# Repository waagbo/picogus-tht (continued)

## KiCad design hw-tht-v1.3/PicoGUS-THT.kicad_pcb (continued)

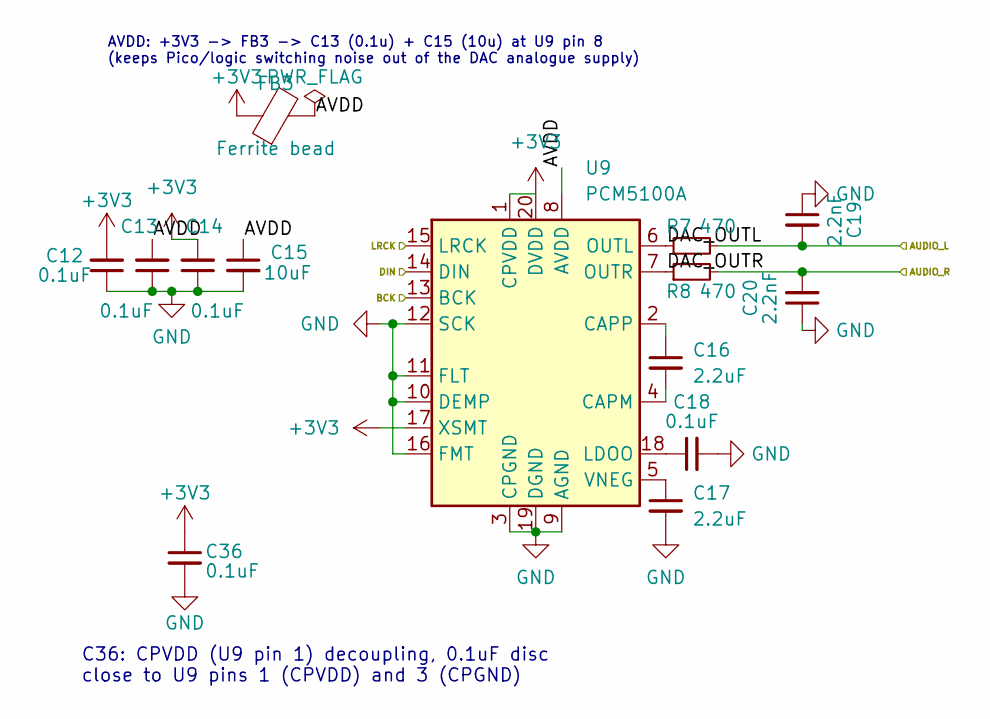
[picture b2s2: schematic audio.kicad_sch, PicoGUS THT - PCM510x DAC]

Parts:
C12, C13, C14, C18, C36: 0.1uF; C_Disc_D5.0mm_W2.5mm_P5.00mm; MPN RDER71H104K0M1H03A; DigiKey 490-9144-1-ND
C15: 10uF; C_Disc_D5.0mm_W2.5mm_P5.00mm; MPN RCER71H106MWK1H03B; DigiKey 490-11888-ND
C16, C17: 2.2uF; C_Disc_D5.0mm_W2.5mm_P5.00mm; MPN FG24X7R1H225KRT06; DigiKey 445-173378-1-ND
C19, C20: 2.2nF; C_Disc_D5.0mm_W2.5mm_P5.00mm; MPN FG28C0G1H222JNT06; DigiKey 445-173487-1-ND
FB3: Ferrite bead; R_Axial_DIN0309_L9.0mm_D3.2mm_P12.70mm_Horizontal; MPN 2743002112; DigiKey 1934-1477-1-ND
R7, R8: 470; R_Axial_DIN0207_L6.3mm_D2.5mm_P10.16mm_Horizontal; MPN RNMF14FTC470R; DigiKey S470CACT-ND
U9: PCM5100A; TSSOP-20_4.4x6.5mm_P0.65mm_HandSolder_TestPads; MPN PCM5100APWR; DigiKey 296-36705-1-ND

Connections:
+3V3: C12.2, C14.2, C36.1, FB3.1, U9.1 (CPVDD), U9.17 (XSMT), U9.20 (DVDD); also elsewhere on the board
/PCM5100 audio/AUDIO_L: C19.2, R7.2; also elsewhere on the board
/PCM5100 audio/AUDIO_R: C20.2, R8.2; also elsewhere on the board
/PCM5100 audio/AVDD: C13.2, C15.1, FB3.2, U9.8 (AVDD)
/PCM5100 audio/DAC_OUTL: R7.1, U9.6 (OUTL)
/PCM5100 audio/DAC_OUTR: R8.1, U9.7 (OUTR)
BCK: U9.13 (BCK); also elsewhere on the board
DIN: U9.14 (DIN); also elsewhere on the board
GND: C12.1, C13.1, C14.1, C15.2, C17.2, C18.2, C19.1, C20.1, C36.2, U9.3 (CPGND), U9.9 (AGND), U9.10 (DEMP), U9.11 (FLT), U9.12 (SCK), U9.16 (FMT), U9.19 (DGND); also elsewhere on the board
LRCK: U9.15 (LRCK); also elsewhere on the board
unnamed: C16.2, U9.4 (CAPM)
unnamed: C16.1, U9.2 (CAPP)
unnamed: C18.1, U9.18 (LDOO)
unnamed: C17.1, U9.5 (VNEG)

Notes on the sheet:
AVDD: +3V3 -> FB3 -> C13 (0.1u) + C15 (10u) at U9 pin 8 (keeps Pico/logic switching noise out of the DAC analogue supply)
C36: CPVDD (U9 pin 1) decoupling, 0.1uF disc close to U9 pins 1 (CPVDD) and 3 (CPGND)

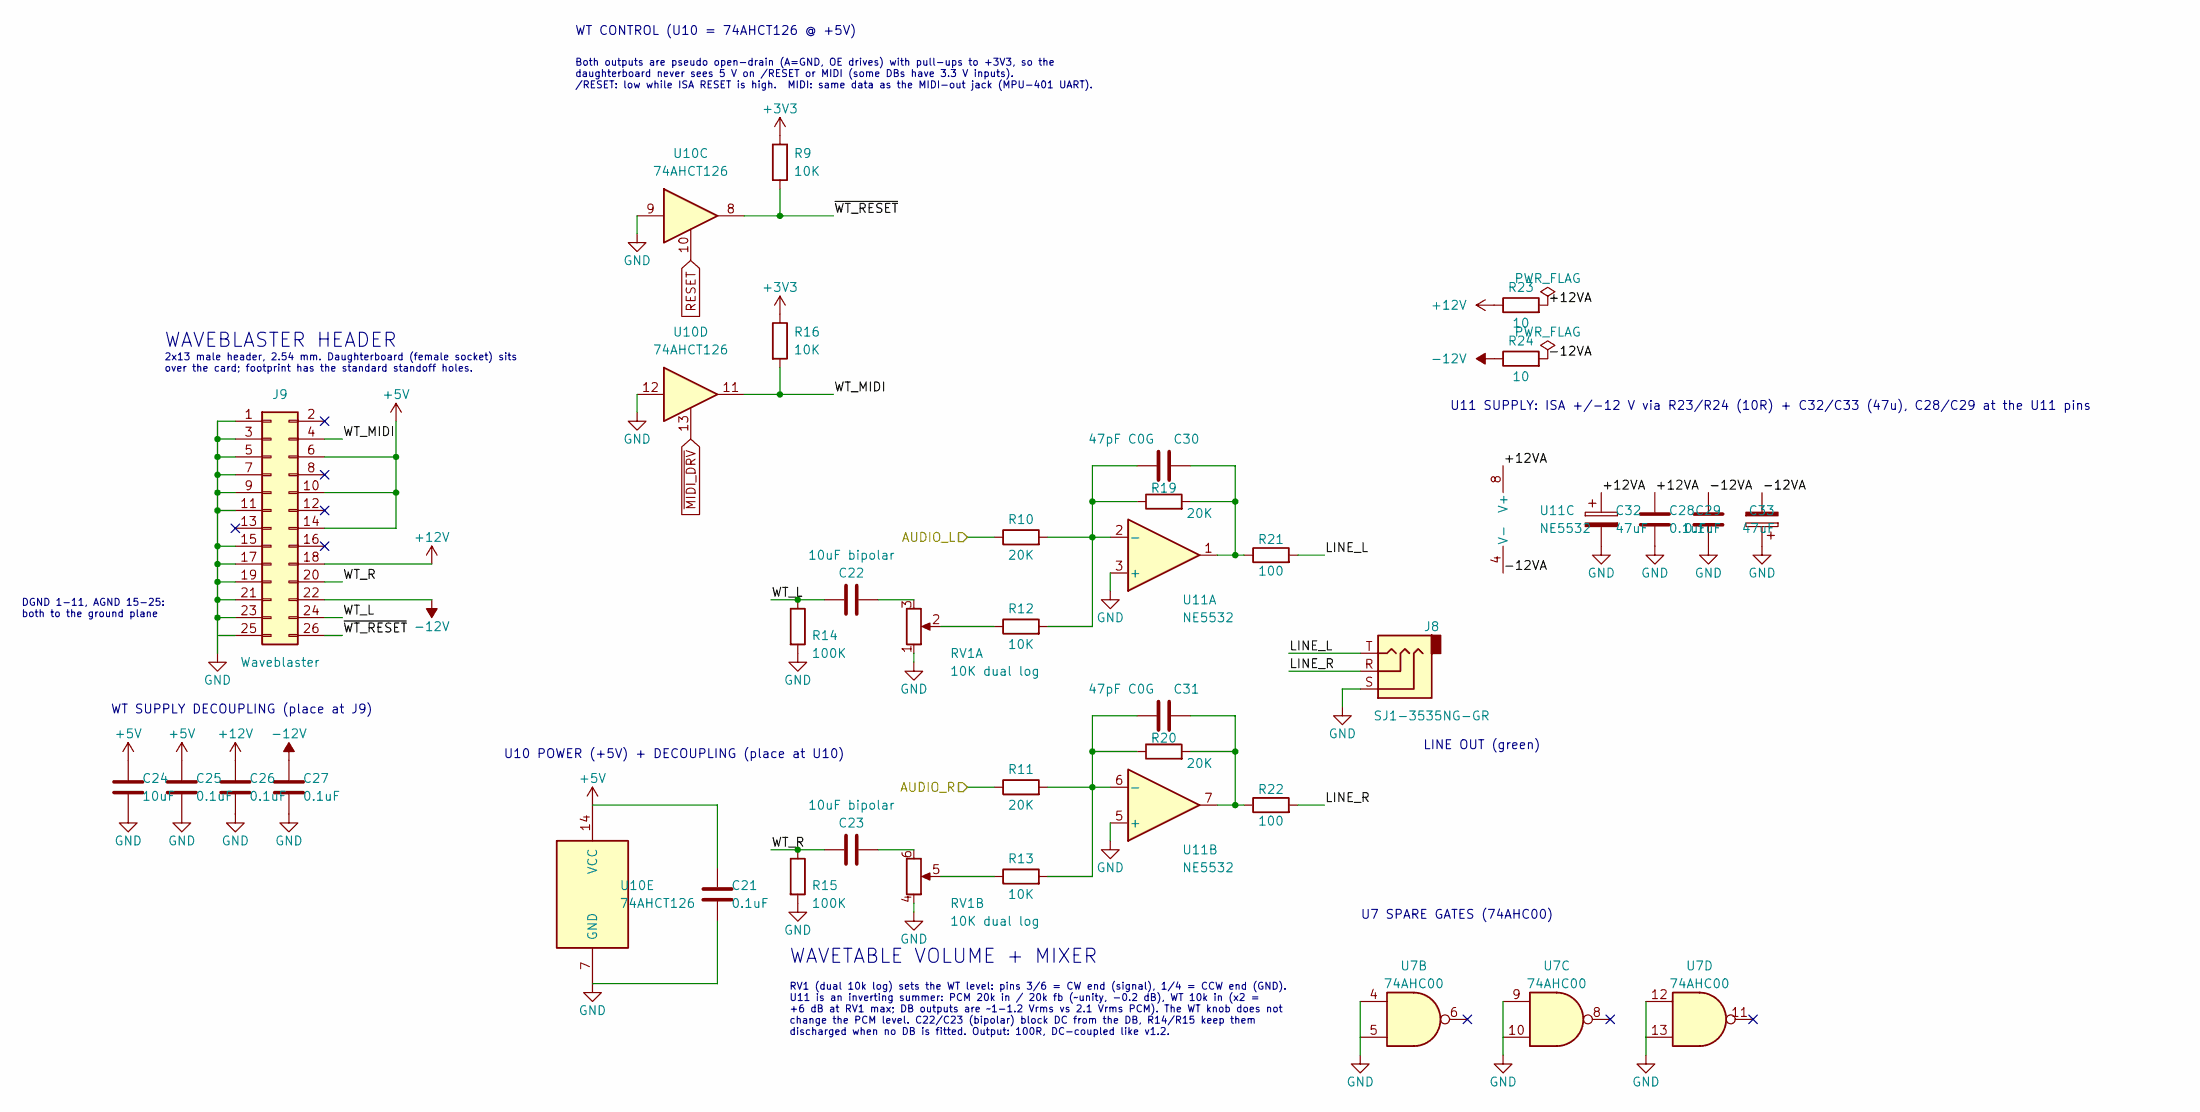
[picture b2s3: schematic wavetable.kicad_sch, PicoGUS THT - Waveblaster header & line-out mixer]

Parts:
C21, C25, C26, C27, C28, C29: 0.1uF; C_Disc_D5.0mm_W2.5mm_P5.00mm; MPN RDER71H104K0M1H03A; DigiKey 490-9144-1-ND
C22, C23: 10uF bipolar; C_Radial_D6.3mm_H11.0mm_P2.50mm; MPN ECE-A1HN100U; DigiKey P1280-ND
C24: 10uF; C_Disc_D5.0mm_W2.5mm_P5.00mm; MPN RCER71H106MWK1H03B; DigiKey 490-11888-ND
C30, C31: 47pF C0G; C_Disc_D5.0mm_W2.5mm_P5.00mm; MPN K470J15C0GF5TH5; DigiKey BC1038CT-ND
C32, C33: 47uF; CP_Radial_D5.0mm_P2.00mm; MPN 35YXJ47M5X11; DigiKey 1189-2919-ND
J8: SJ1-3535NG-GR; Jack_3.5mm_CUI_SJ1-3535NG_Horizontal; MPN SJ1-3535NG-GR; DigiKey CP1-3535NG-GR-ND
J9: Waveblaster; Wavetable_NoMountingHoles; MPN 77313-118-26LF; DigiKey 609-5706-ND
R9, R12, R13, R16: 10K; R_Axial_DIN0207_L6.3mm_D2.5mm_P10.16mm_Horizontal; MPN MFR-25FBF52-10K; DigiKey 10.0KXBK-ND
R10, R11, R19, R20: 20K; R_Axial_DIN0207_L6.3mm_D2.5mm_P10.16mm_Horizontal; MPN MFR-25FBF52-20K; DigiKey 20.0KXBK-ND
R14, R15: 100K; R_Axial_DIN0207_L6.3mm_D2.5mm_P10.16mm_Horizontal; MPN MFR-25FBF52-100K; DigiKey 100KXBK-ND
R21, R22: 100; R_Axial_DIN0207_L6.3mm_D2.5mm_P10.16mm_Horizontal; MPN MFR-25FBF52-100R; DigiKey 100XBK-ND
R23, R24: 10; R_Axial_DIN0207_L6.3mm_D2.5mm_P10.16mm_Horizontal; MPN MFR-25FBF52-10R; DigiKey 10.0XBK-ND
RV1: 10K dual log; Potentiometer_Alps_RK097_Dual_Horizontal_Switch; MPN PTD902-2015F-A103; DigiKey PTD902-2015F-A103-ND
U7: 74AHC00; DIP-14_W7.62mm; MPN SN74AHC00N; DigiKey 296-4510-5-ND
U10: 74AHCT126; DIP-14_W7.62mm; MPN SN74AHCT126N; DigiKey 296-4659-5-ND
U11: NE5532; DIP-8_W7.62mm; MPN NE5532P; DigiKey 296-1410-5-ND

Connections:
+3V3: R9.1, R16.1; also elsewhere on the board
+5V: C21.1, C24.1, C25.1, J9.6, J9.10, J9.14, U10.14 (VCC); also elsewhere on the board
+12V: C26.1, J9.18, R23.1; also elsewhere on the board
-12V: C27.1, J9.22, R24.1; also elsewhere on the board
/PCM5100 audio/AUDIO_L: R10.1; also elsewhere on the board
/PCM5100 audio/AUDIO_R: R11.1; also elsewhere on the board
/Wavetable & line out/+12VA: C28.1, C32.1, R23.2, U11.8 (V+)
/Wavetable & line out/-12VA: C29.2, C33.2, R24.2, U11.4 (V-)
/Wavetable & line out/LINE_L: J8.T, R21.2
/Wavetable & line out/LINE_R: J8.R, R22.2
/Wavetable & line out/WT_L: C22.1, J9.24, R14.1
/Wavetable & line out/WT_MIDI: J9.4, R16.2, U10.11
/Wavetable & line out/WT_R: C23.1, J9.20, R15.1
/Wavetable & line out/~WT_RESET: J9.26, R9.2, U10.8
GND: C21.2, C24.2, C25.2, C26.2, C27.2, C28.2, C29.1, C32.2, C33.1, J8.S, J9.1, J9.3, J9.5, J9.7, J9.9, J9.11, J9.15, J9.17, J9.19, J9.21, J9.23, J9.25, R14.2, R15.2, RV1.1, RV1.4, U7.4, U7.5, U7.9, U7.10, U7.12, U7.13, U10.7 (GND), U10.9, U10.12, U11.3 (+), U11.5 (+); also elsewhere on the board
unnamed: C22.2, RV1.3
unnamed: C23.2, RV1.6
unnamed: C30.2, R19.2, R21.1, U11.1
unnamed: C31.2, R20.2, R22.1, U11.7
unnamed: R12.1, RV1.2
unnamed: R13.1, RV1.5
unnamed: C30.1, R10.2, R12.2, R19.1, U11.2 (-)
unnamed: C31.1, R11.2, R13.2, R20.1, U11.6 (-)
RESET: U10.10; also elsewhere on the board
~MIDI_DRV: U10.13; also elsewhere on the board

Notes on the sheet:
DGND 1-11, AGND 15-25: both to the ground plane
WAVEBLASTER HEADER
2x13 male header, 2.54 mm. Daughterboard (female socket) sits over the card; footprint has the standard standoff holes.
WT SUPPLY DECOUPLING (place at J9)
U10 POWER (+5V) + DECOUPLING (place at U10)
WT CONTROL (U10 = 74AHCT126 @ +5V)
Both outputs are pseudo open-drain (A=GND, OE drives) with pull-ups to +3V3, so the daughterboard never sees 5 V on /RESET or MIDI (some DBs have 3.3 V inputs). /RESET: low while ISA RESET is high. MIDI: same data as the MIDI-out jack (MPU-401 UART).
U11 SUPPLY: ISA +/-12 V via R23/R24 (10R) + C32/C33 (47u), C28/C29 at the U11 pins
WAVETABLE VOLUME + MIXER
RV1 (dual 10k log) sets the WT level: pins 3/6 = CW end (signal), 1/4 = CCW end (GND). U11 is an inverting summer: PCM 20k in / 20k fb (~unity, -0.2 dB), WT 10k in (x2 = +6 dB at RV1 max; DB outputs are ~1-1.2 Vrms vs 2.1 Vrms PCM). The WT knob does not change the PCM level. C22/C23 (bipolar) block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
LINE OUT (green)
U7 SPARE GATES (74AHC00)

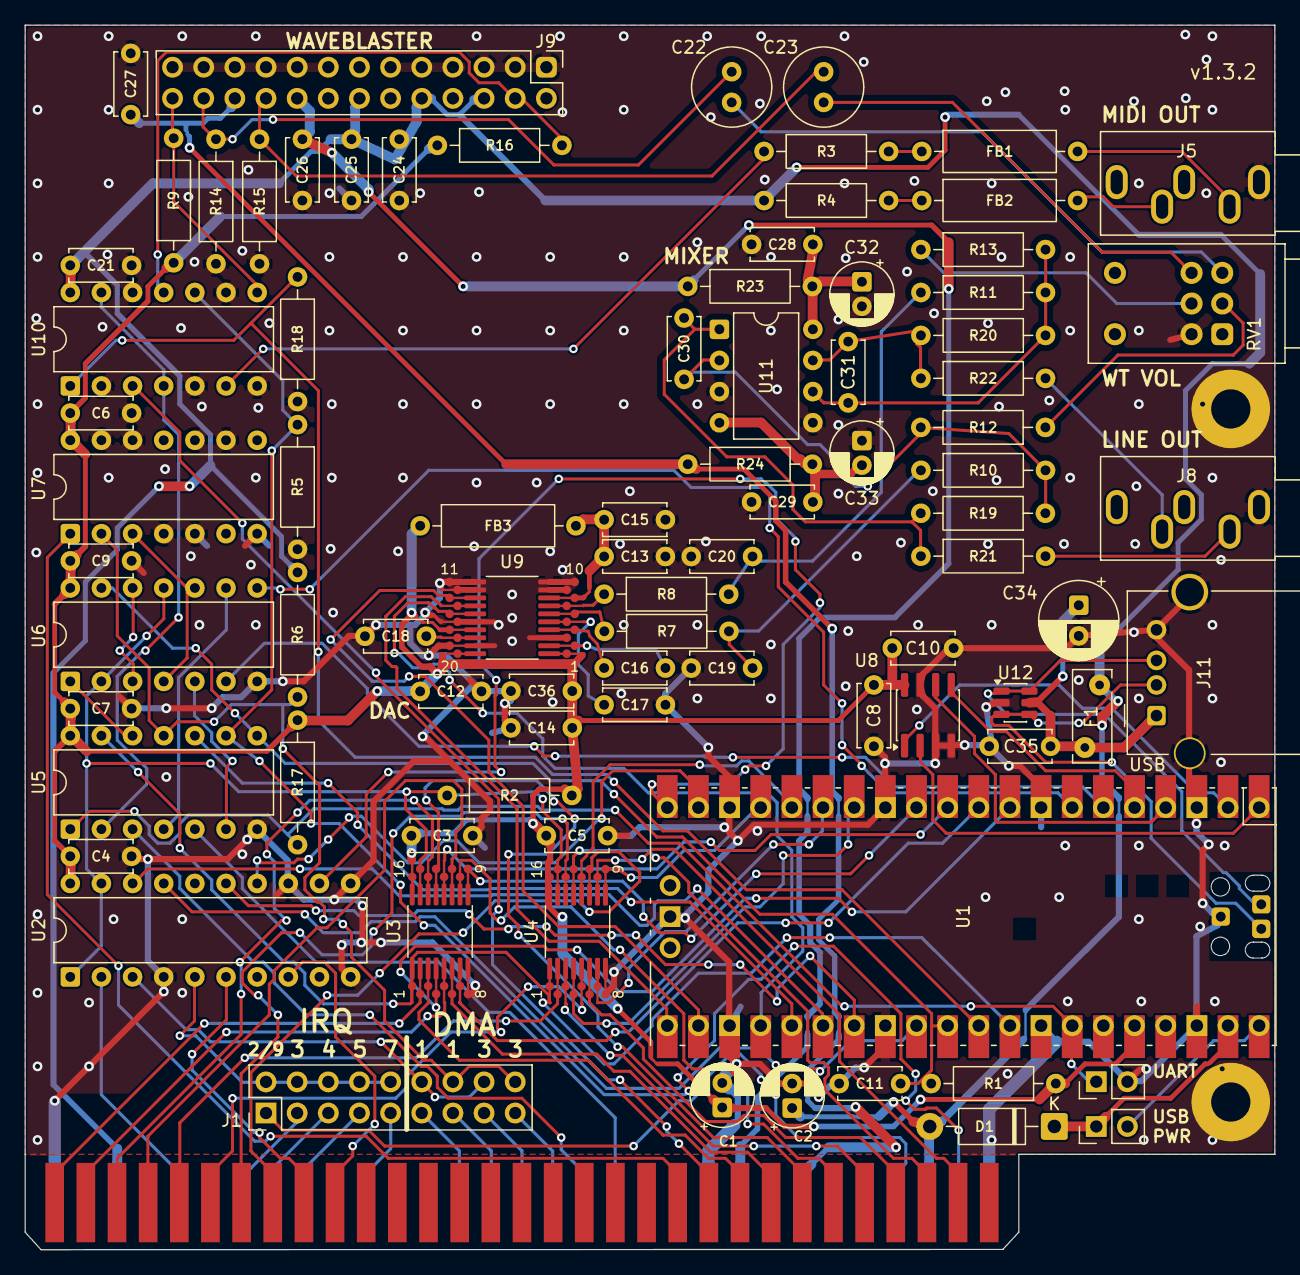
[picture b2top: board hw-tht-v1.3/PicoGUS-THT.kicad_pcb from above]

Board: 2 copper layers, 101.9 x 99.8 mm, 88 parts (0 on the bottom side), 110 nets.

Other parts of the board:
C34: 220uF; CP_Radial_D6.3mm_P2.50mm
C35: 0.1uF; C_Disc_D5.0mm_W2.5mm_P5.00mm
F1: 0.5A PTC; Fuse_Bourns_MF-RHT050
J11: USB-A; USB_A_Molex_67643_Horizontal
U12: USBLC6-2SC6; SOT-23-6

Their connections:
+5V: F1.1; also elsewhere on the board
/USB host port/VBUS_USB: C34.1, C35.1, F1.2, J11.1, U12.5
GND: C34.2, C35.2, J11.4, J11.SH, U12.2; also elsewhere on the board
USB_DM: J11.2, U12.3, U12.4; also elsewhere on the board
USB_DP: J11.3, U12.1, U12.6; also elsewhere on the board

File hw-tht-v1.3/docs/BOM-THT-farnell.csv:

Quantity,Manufacturer Part Number,Manufacturer,Customer Part Number,Description
1,SC0915,Raspberry Pi,PicoGUS-THT-1.3.2: U1,Raspberry Pi Pico
1,SN74AHC244N,Texas Instruments,PicoGUS-THT-1.3.2: U2,74AHC244
2,SN74CB3T3257PWR,Texas Instruments,"PicoGUS-THT-1.3.2: U3,U4",SN74CB3T3257
1,SN74AHC14N,Texas Instruments,PicoGUS-THT-1.3.2: U5,74AHC14
2,SN74AHC00N,Texas Instruments,"PicoGUS-THT-1.3.2: U6,U7",74AHC00
1,APS6404L-3SQR-SN,AP Memory,PicoGUS-THT-1.3.2: U8,APS6404L-3SQR-SN
1,PCM5100APWR,Texas Instruments,PicoGUS-THT-1.3.2: U9,PCM5100A
1,SN74AHCT126N,Texas Instruments,PicoGUS-THT-1.3.2: U10,74AHCT126
1,1N5819RLG,onsemi,PicoGUS-THT-1.3.2: D1,1N5819
2,RNMF14FTC220R,Stackpole,"PicoGUS-THT-1.3.2: R3,R4",220R
2,RNMF14FTC470R,Stackpole,"PicoGUS-THT-1.3.2: R7,R8",470R
1,MFR-25FBF52-1K,Yageo,PicoGUS-THT-1.3.2: R1,1k
5,MFR-25FBF52-10K,Yageo,"PicoGUS-THT-1.3.2: R9,R12,R13,R16,R17",10k
4,MFR-25FBF52-20K,Yageo,"PicoGUS-THT-1.3.2: R10,R11,R19,R20",20k
3,MFR-25FBF52-15K,Yageo,"PicoGUS-THT-1.3.2: R2,R5,R6",15k
20,RDER71H104K0M1H03A,Murata,"PicoGUS-THT-1.3.2: C3-9,11-14,18,21,25-29,35,36",0.1uF
1,RDER71H105K2M1H03A,Murata,PicoGUS-THT-1.3.2: C10,1uF
2,FG24X7R1H225KRT06,TDK,"PicoGUS-THT-1.3.2: C16,C17",2.2uF
2,RCER71H106MWK1H03B,Murata,"PicoGUS-THT-1.3.2: C15,C24",10uF
2,FG28C0G1H222JNT06,TDK,"PicoGUS-THT-1.3.2: C19,C20",2.2nF C0G
4,35YXJ47M5X11,Rubycon,"PicoGUS-THT-1.3.2: C1,C2,C32,C33",47uF
2,ECE-A1HN100U,Panasonic,"PicoGUS-THT-1.3.2: C22,C23",10uF bipolar
3,2743002112,Fair-Rite,"PicoGUS-THT-1.3.2: FB1,FB2,FB3",Ferrite bead
1,PTD902-2015F-A103,Bourns,PicoGUS-THT-1.3.2: RV1,10k dual log
1,77313-118-18LF,Amphenol ICC (FCI),PicoGUS-THT-1.3.2: J1,"2x9 header, gold"
4,M7582-05,Harwin,"PicoGUS-THT-1.3.2: J1,J7 shunts",2.54mm jumper shunt
2,77311-118-02LF,Amphenol ICC (FCI),"PicoGUS-THT-1.3.2: J6,J7","1x2 header, gold"
1,SJ1-3535NG,Same Sky (CUI),PicoGUS-THT-1.3.2: J5,SJ1-3535NG (black)
1,SJ1-3535NG-GR,Same Sky (CUI),PicoGUS-THT-1.3.2: J8,SJ1-3535NG-GR (green)
1,77313-118-26LF,Amphenol ICC (FCI),PicoGUS-THT-1.3.2: J9,"Waveblaster 2x13 male, gold"
1,0676430910,Molex,PicoGUS-THT-1.3.2: J11,USB-A receptacle
1,MF-R050,Bourns,PicoGUS-THT-1.3.2: F1,0.5A PTC
1,16ZLH220MEFC6.3X11,Rubycon,PicoGUS-THT-1.3.2: C34,220uF
1,USBLC6-2SC6,STMicroelectronics,PicoGUS-THT-1.3.2: U12 (optional),USBLC6-2SC6
1,NE5532P,Texas Instruments,PicoGUS-THT-1.3.2: U11,NE5532
3,MFR-25FBF52-100K,Yageo,"PicoGUS-THT-1.3.2: R14,R15,R18",100k
2,MFR-25FBF52-10R,Yageo,"PicoGUS-THT-1.3.2: R23,R24",10R
2,MFR-25FBF52-100R,Yageo,"PicoGUS-THT-1.3.2: R21,R22",100R
2,K470J15C0GF5TH5,Vishay,"PicoGUS-THT-1.3.2: C30,C31",47pF C0G

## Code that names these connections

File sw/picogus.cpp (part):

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#ifdef ASYNC_UART
#include "stdio_async_uart.h"
#endif 
// UART_TX_PIN is defined in isa_io.pio.h
#define UART_RX_PIN (-1)
#define UART_ID     uart0
#define BAUD_RATE   230400
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    busy_wait_ms(250);
    overclock_370mhz();
#ifdef ASYNC_UART
    stdio_async_uart_init_full(UART_ID, BAUD_RATE, UART_TX_PIN, UART_RX_PIN);
#else
    stdio_init_all();
#endif
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    if (*reset_reason & PLATFORM_CHIP_RESET_HAD_POWER_ON_BITS) {
        DBG_PUTS("I was reset due to power on reset or brownout detection.");
    } else if (*reset_reason & PLATFORM_CHIP_RESET_HAD_RUN_PIN_BITS) {
        DBG_PUTS("I was reset due to the RUN pin (either manually or due to ISA RESET signal)");
    } else if(*reset_reason & PLATFORM_CHIP_RESET_HAD_DEBUG_BITS) {
        DBG_PUTS("I was reset due the debug port");
    }
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    gpio_set_dir(PICOGUS_BOOTROM_EN_PIN, GPIO_OUT);
#endif
#else
    // Determine board type. GPIO 29 is grounded on PicoGUS v2.0, and on a Pico, it's VSYS/3 (~1.666V)
    // GPIO 25 must be high to read GPIO 29 on the Pico W
    gpio_init(25);
    gpio_set_dir(25, GPIO_OUT);
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    if (BOARD_TYPE == PICO_BASED) {
        // Original hardware drives MIDI directly from RP2040. Newer HW uses an open drain inverter
        // PicoGUS v1.2 also uses an open drain but we can't detect that particular board
        gpio_set_drive_strength(UART_TX_PIN, GPIO_DRIVE_STRENGTH_12MA);
    }
    gpio_set_function(UART_TX_PIN, GPIO_FUNC_UART);
#endif // SOUND_MPU

#ifdef PSRAM_CORE0
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        platform_gpio_enable_input(i);
        gpio_disable_pulls(i);
    }
    platform_gpio_enable_input(IOW_PIN);
    platform_gpio_enable_input(IOR_PIN);
    platform_gpio_enable_input(DACK_PIN);
    gpio_disable_pulls(IOW_PIN);
    gpio_disable_pulls(IOR_PIN);
    gpio_pull_down(IOCHRDY_PIN);
    gpio_set_dir(IOCHRDY_PIN, GPIO_OUT);

    DBG_PUTS("Enabling bus transceivers...");
    // waggle ADS to set BUSOE latch
    gpio_init(ADS_PIN);
    gpio_set_dir(ADS_PIN, GPIO_OUT);
    gpio_put(ADS_PIN, 1);
    busy_wait_ms(10);
    gpio_put(ADS_PIN, 0);

    DBG_PUTS("Starting ISA bus PIO...");
    // gpio_set_drive_strength(ADS_PIN, GPIO_DRIVE_STRENGTH_12MA);
    gpio_set_slew_rate(ADS_PIN, GPIO_SLEW_RATE_FAST);

    uint iow_offset = pio_add_program(pio0, &iow_program);
    pio_sm_claim(pio0, IOW_PIO_SM);
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
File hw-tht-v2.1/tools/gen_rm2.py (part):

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
SIGNALS = {
    1: 'GND', 2: 'NC', 3: 'SCLK', 4: 'GND', 5: 'DATA_IN', 6: 'DATA_OUT', 7: 'GND',
    8: 'GPIO0', 9: 'CS', 10: 'nIRQ', 11: 'GND', 12: 'WL_ON', 13: 'BT_ON', 14: 'VDDIO',
    15: 'GND', 16: 'VIN', 17: 'GPIO2', 18: 'GPIO1', 19: 'NC', 20: 'NC', 21: 'GND',
}


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    F = '(effects (font (size 1.27 1.27)))'
    left = [(3, 'SCLK', 'input'), (5, 'DATA_IN', 'input'), (6, 'DATA_OUT', 'output'), (10, '~{IRQ}', 'output'),
            (9, 'CS', 'input'), (12, 'WL_ON', 'input'), (13, 'BT_ON', 'input')]
    right = [(16, 'VIN', 'power_in'), (14, 'VDDIO', 'power_in'), None, (8, 'GPIO0', 'bidirectional'),
             (18, 'GPIO1', 'bidirectional'), (17, 'GPIO2', 'bidirectional'), None, (2, 'NC', 'no_connect'),
             (19, 'NC', 'no_connect'), (20, 'NC', 'no_connect')]
    gnd = [1, 4, 7, 11, 15, 21]
    s = []
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
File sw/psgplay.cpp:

/*
 *  Copyright (C) 2022-2024  Ian Scott
 *
 *  This program is free software; you can redistribute it and/or modify
 *  it under the terms of the GNU General Public License as published by
 *  the Free Software Foundation; either version 2 of the License, or
 *  (at your option) any later version.
 *
 *  This program is distributed in the hope that it will be useful,
 *  but WITHOUT ANY WARRANTY; without even the implied warranty of
 *  MERCHANTABILITY or FITNESS FOR A PARTICULAR PURPOSE.  See the
 *  GNU General Public License for more details.
 *
 *  You should have received a copy of the GNU General Public License along
 *  with this program; if not, write to the Free Software Foundation, Inc.,
 *  51 Franklin Street, Fifth Floor, Boston, MA 02110-1301, USA.
 */

#include "include/pg_debug.h"

#if PICO_ON_DEVICE
#include "hardware/clocks.h"
#include "hardware/structs/clocks.h"
#include "hardware/pwm.h"
#include "hardware/pio.h"
#endif

#include "pico/stdlib.h"
#include "audio/audio_i2s_minimal.h"
#include "audio/volctrl.h"
#include "audio/clamp.h"

#include "square/square.h"

#include "include/cmd_buffers.h"

#if SOUND_TANDY
extern tandy_buffer_t tandy_buffer;
#endif
#if SOUND_CMS
extern cms_buffer_t cms_buffer;
#endif

extern uint LED_PIN;

#ifdef USB_STACK
#include "tusb.h"
#endif
#if defined(USB_MOUSE) || defined(SOUND_MPU)
#include "system/pico_pic.h"
#endif

#ifdef USB_MOUSE
#include "mouse/8250uart.h"
#include "mouse/sermouse.h"
#endif

#if PICO_ON_DEVICE
#include "pico/binary_info.h"
bi_decl(bi_3pins_with_names(PICO_AUDIO_I2S_DATA_PIN, "I2S DIN", PICO_AUDIO_I2S_CLOCK_PIN_BASE, "I2S BCK", PICO_AUDIO_I2S_CLOCK_PIN_BASE+1, "I2S LRCK"));
#endif

#ifdef SOUND_MPU
#include "system/flash_settings.h"
extern Settings settings;
#include "mpu401/export.h"
#endif

#ifdef WEBSERVER
#include "web/web.h"
#endif

#define audio_pio __CONCAT(pio, PICO_AUDIO_I2S_PIO)

static void init_audio(void) {
    const audio_i2s_config_t config = {
            .data_pin = PICO_AUDIO_I2S_DATA_PIN,
            .clock_pin_base = PICO_AUDIO_I2S_CLOCK_PIN_BASE,
            .dma_channel = 6,
            .pio_sm = PICO_AUDIO_I2S_SM,
    };
    audio_i2s_minimal_setup(&config, 44100);
}

#if SOUND_TANDY
static tandysound_t tandysound;
#endif
#if SOUND_CMS
static cms_t cms;
#endif

// Setup values for audio sample clock
static constexpr uint32_t clocks_per_sample_minus_one = (RP2_CLOCK_SPEED * 1000u / 44100) - 1;
static constexpr uint pwm_slice_num = 4; // slices 0-3 are taken by USB joystick support

// PSG generation is cheap (phase accumulators + volume lookups per voice), so
// synthesize directly in the ISR — no intermediate FIFO needed.
void audio_sample_handler(void) {
    pwm_clear_irq(pwm_slice_num);

    int32_t buf[2] = {0, 0};
#if SOUND_TANDY
    tandysound.generator().generate_frames(buf, 1);
#endif
#if SOUND_CMS
    cms.generator(0).generate_frames(buf, 1);
    cms.generator(1).generate_frames(buf, 1);
#endif
    int32_t sample_l = scale_sample(clamp16(buf[0]), volume.psg, 0);
    int32_t sample_r = scale_sample(clamp16(buf[1]), volume.psg, 0);
    sample_l = clamp16(sample_l);
    sample_r = clamp16(sample_r);

    audio_pio->txf[PICO_AUDIO_I2S_SM] = ((sample_l & 0xFFFF) | (sample_r << 16));
}

void play_psg() {
    DBG_PUTS("starting core 1 psg");
    // flash_safe_execute_core_init();

#if defined(USB_MOUSE) || defined(SOUND_MPU)
    // Init PIC on this core so it handles timers
    PIC_Init();
    DBG_PUTS("pic inited on core 1");
#endif
#ifdef USB_STACK
    // Init TinyUSB for joystick support
    tuh_init(BOARD_TUH_RHPORT);
    // Pump USB events for ~500 ms so any device already connected at boot
    // is fully enumerated before the audio loop starts.
    {
        uint32_t deadline = time_us_32() + 500000u;
        while (time_us_32() < deadline) tuh_task();
    }
#endif

#ifdef SOUND_MPU
    MPU401_Init(settings.MPU.delaySysex, settings.MPU.fakeAllNotesOff, settings.MPU.waitBusyStatus);
#endif

    init_audio();
    set_volume(CMD_PSGVOL);

    // Use the PWM peripheral to trigger an IRQ at 44100Hz
    pwm_config pwm_c = pwm_get_default_config();
    pwm_config_set_wrap(&pwm_c, clocks_per_sample_minus_one);
    pwm_init(pwm_slice_num, &pwm_c, false);
    pwm_set_irq_enabled(pwm_slice_num, true);
    irq_set_exclusive_handler(PWM_IRQ_WRAP, audio_sample_handler);
    irq_set_priority(PWM_IRQ_WRAP, PICO_LOWEST_IRQ_PRIORITY);
    irq_set_enabled(PWM_IRQ_WRAP, true);
    pwm_set_enabled(pwm_slice_num, true);

    for (;;) {
        bool notfirst = false;
#if SOUND_TANDY
        while (tandy_buffer.tail != tandy_buffer.head) {
            if (!notfirst) {
                gpio_xor_mask(LED_PIN);
                notfirst = true;
            }
            tandysound.write_register(0, tandy_buffer.cmds[tandy_buffer.tail]);
            ++tandy_buffer.tail;
        }
#endif // SOUND_TANDY
#if SOUND_CMS
        while (cms_buffer.tail != cms_buffer.head) {
            if (!notfirst) {
                gpio_xor_mask(LED_PIN);
                notfirst = true;
            }
            auto cmd = cms_buffer.cmds[cms_buffer.tail];
            if (cmd.addr & 1) {
                cms.write_addr(cmd.addr, cmd.data);
            } else {
                cms.write_data(cmd.addr, cmd.data);
            }
            ++cms_buffer.tail;
        }
#endif

#ifdef USB_STACK
        // Service TinyUSB events
        tuh_task();
#endif
#ifdef USB_MOUSE
        // mouse task
        sermouse_core1_task();

        // uart emulation task
        uartemu_core1_task();
#endif
#ifdef SOUND_MPU
        send_midi_bytes(8);
#endif
#ifdef WEBSERVER
        // Lowest priority work: PSG audio is synthesized in an interrupt
        web_task();
#endif
    }
}
